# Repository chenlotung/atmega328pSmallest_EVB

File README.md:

# 自已的開發板自己做工作坊
## 裸線焊接你的Atmega328p迷你開發板
[工作訪計畫書_hackmd](https://hackmd.io/4ialXZNIRGWbu7fYnHaSIw?both)

[單層板設計_kicad_github](https://github.com/chenlotung/atmega328pSmallest_EVB)
- kicad 3d模型圖
- 

# 所需材料(粗估成本:每份230元不含運，不含uno板及焊接工具)
- [ ] arduino uno r3 開發板
- [ ] cp2102 usb to ttl 模組
- [ ] atmega328p dip 28pin
- [ ] 5x7cm以上，單面或雙面玻纖萬孔板
- [ ] 16MHZ 石英震盪器
- [ ] 18-22pF陶瓷電容*2
- [ ] 長杜邦針or母座*28
- [ ] 5mmLED
- [ ] 5X6mm直插式按鈕*2
- [ ] 電阻(下列各一)
- 1k,1M.10M 
- [ ] 鍍錫裸線
- [ ] 焊錫

# 實驗步驟
1. 元件測試
    -  led、按鈕通斷測試
    -  電容值電阻值紀錄
    -  使用麵包板與uno燒錄bootloader 確認晶片功能正常

定位各元件位置，（參照參考資料之位置圖與走線圖)

未完待續...................
未完成項目:底座製圖(四角拔模圓柱，矩形底座)
# 參考資料
## 照片 
- atmega328p pin out

- arduino uno r3 schematic

- 萬孔板正面元件位置圖
- 

- 萬孔板背面走線圖
- 

## 影片

* [燒錄BootLoader](https://www.youtube.com/watch?v=smr9EddIL3Q)
* [上傳程式](https://www.youtube.com/watch?v=cvyq-qohljg)
## 文章
https://www.instructables.com/%E8%87%AA%E9%80%A0%E4%BD%A0%E7%9A%84Arduino-UNO%E6%9D%BF/
https://www.microchip.com/en-us/product/ATmega328P#document-table
https://www.electroschematics.com/diy-arduino-making-your-own-arduino/
https://makersportal.com/blog/2018/3/15/arduino-internet-of-things-part-1-burning-the-arduino-bootloader-onto-a-blank-atmega328p-chip-using-the-arduino-uno

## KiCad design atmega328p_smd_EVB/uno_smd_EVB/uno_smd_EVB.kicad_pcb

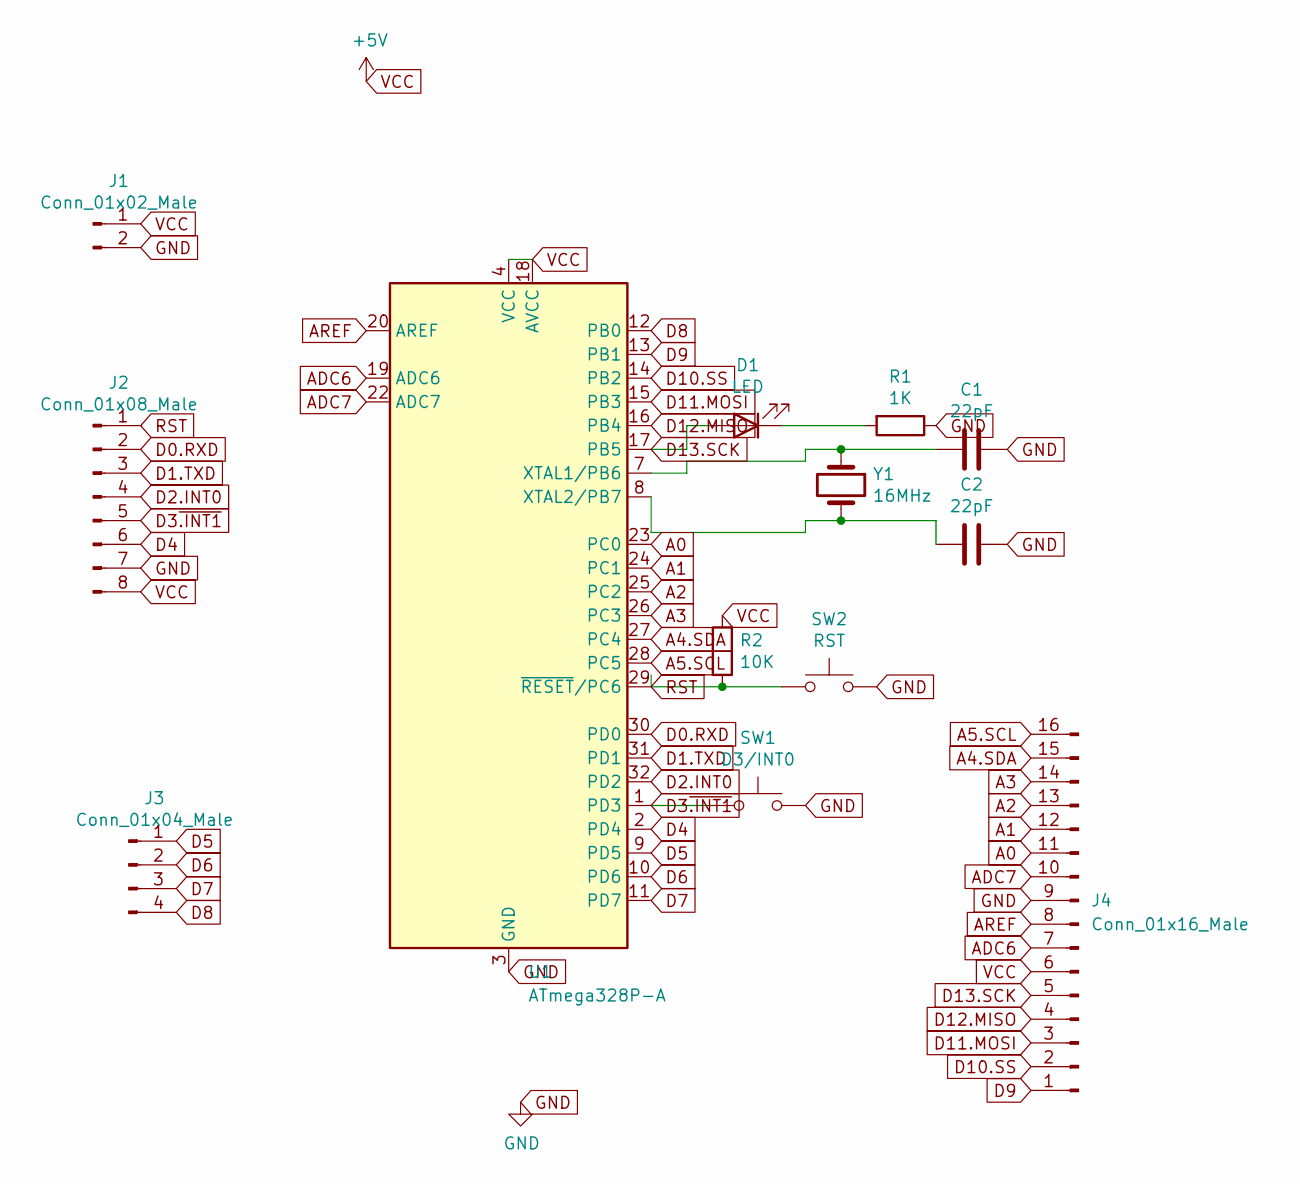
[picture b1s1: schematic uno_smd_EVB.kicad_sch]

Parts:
C1, C2: 22pF; C_0805_2012Metric_Pad1.18x1.45mm_HandSolder
D1: LED; LED_0805_2012Metric_Pad1.15x1.40mm_HandSolder
J1: Conn_01x02_Male; PinHeader_1x02_P2.54mm_Vertical
J2: Conn_01x08_Male; PinHeader_1x08_P2.54mm_Vertical
J3: Conn_01x04_Male; PinHeader_1x04_P2.54mm_Vertical
J4: Conn_01x16_Male; PinHeader_1x16_P2.54mm_Vertical
R1: 1K; R_0805_2012Metric_Pad1.20x1.40mm_HandSolder
R2: 10K; R_0805_2012Metric_Pad1.20x1.40mm_HandSolder
SW1: D3/INT0; SW_SPST_TL3342
SW2: RST; SW_SPST_TL3342
U1: ATmega328P-A; TQFP-32_7x7mm_P0.8mm
Y1: 16MHz; Crystal_SMD_HC49-SD

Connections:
A0: J4.11, U1.23 (PC0)
A1: J4.12, U1.24 (PC1)
A2: J4.13, U1.25 (PC2)
A3: J4.14, U1.26 (PC3)
A4.SDA: J4.15, U1.27 (PC4)
A5.SCL: J4.16, U1.28 (PC5)
ADC6: J4.7, U1.19 (ADC6)
ADC7: J4.10, U1.22 (ADC7)
AREF: J4.8, U1.20 (AREF)
D0.RXD: J2.2, U1.30 (PD0)
D1.TXD: J2.3, U1.31 (PD1)
D2.INT0: J2.4, U1.32 (PD2)
D3~.INT1: J2.5, SW1.1, U1.1 (PD3)
D4: J2.6, U1.2 (PD4)
D5~{: J3.1, U1.9 (PD5)
D6: J3.2, U1.10 (PD6)
D7: J3.3, U1.11 (PD7)
D8: J3.4, U1.12 (PB0)
D9: J4.1, U1.13 (PB1)
D10.SS: J4.2, U1.14 (PB2)
D11.MOSI: J4.3, U1.15 (PB3)
D12.MISO: J4.4, U1.16 (PB4)
D13.SCK: D1.2 (A), J4.5, U1.17 (PB5)
GND: C1.1, C2.1, J1.2, J2.7, J4.9, R1.1, SW1.2, SW2.2, U1.3 (GND), U1.5 (GND), U1.21 (GND)
unnamed: C1.2, U1.7 (XTAL1/PB6), Y1.1
unnamed: C2.2, U1.8 (XTAL2/PB7), Y1.2
unnamed: D1.1 (K), R1.2
RST: J2.1, R2.2, SW2.1, U1.29 (~RESET/PC6)
VCC: J1.1, J2.8, J4.6, R2.1, U1.4 (VCC), U1.6 (VCC), U1.18 (AVCC)

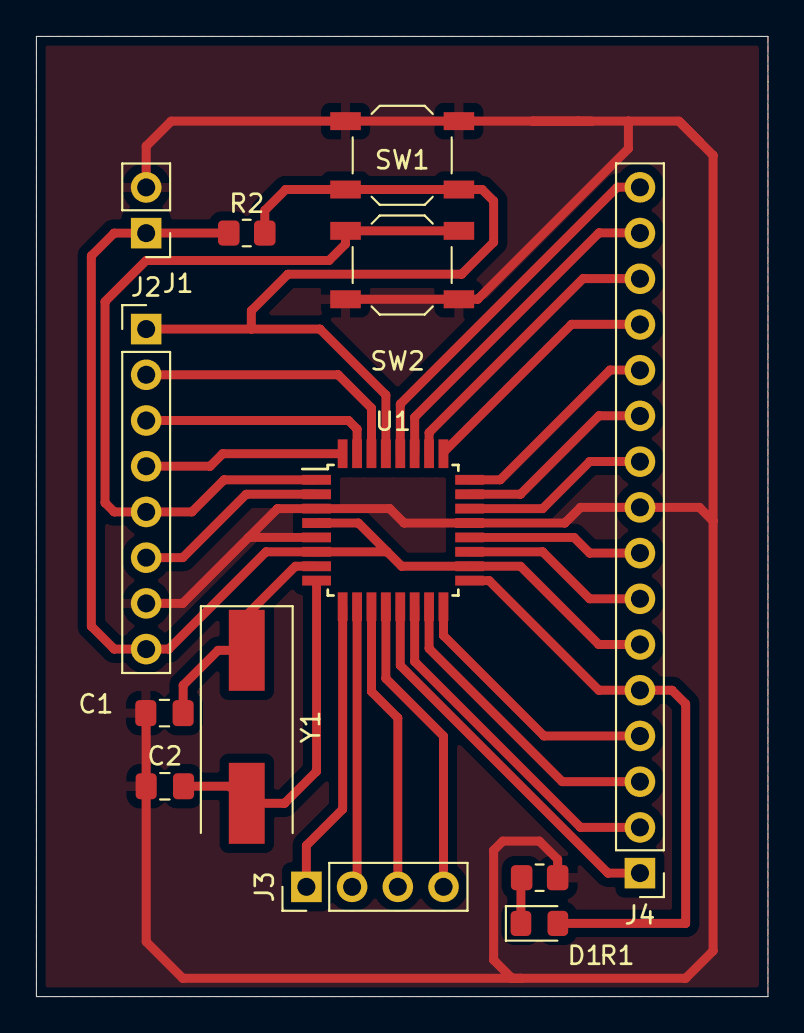
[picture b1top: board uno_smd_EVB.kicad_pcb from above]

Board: 2 copper layers, 40.6 x 53.3 mm, 13 parts (0 on the bottom side), 29 nets.

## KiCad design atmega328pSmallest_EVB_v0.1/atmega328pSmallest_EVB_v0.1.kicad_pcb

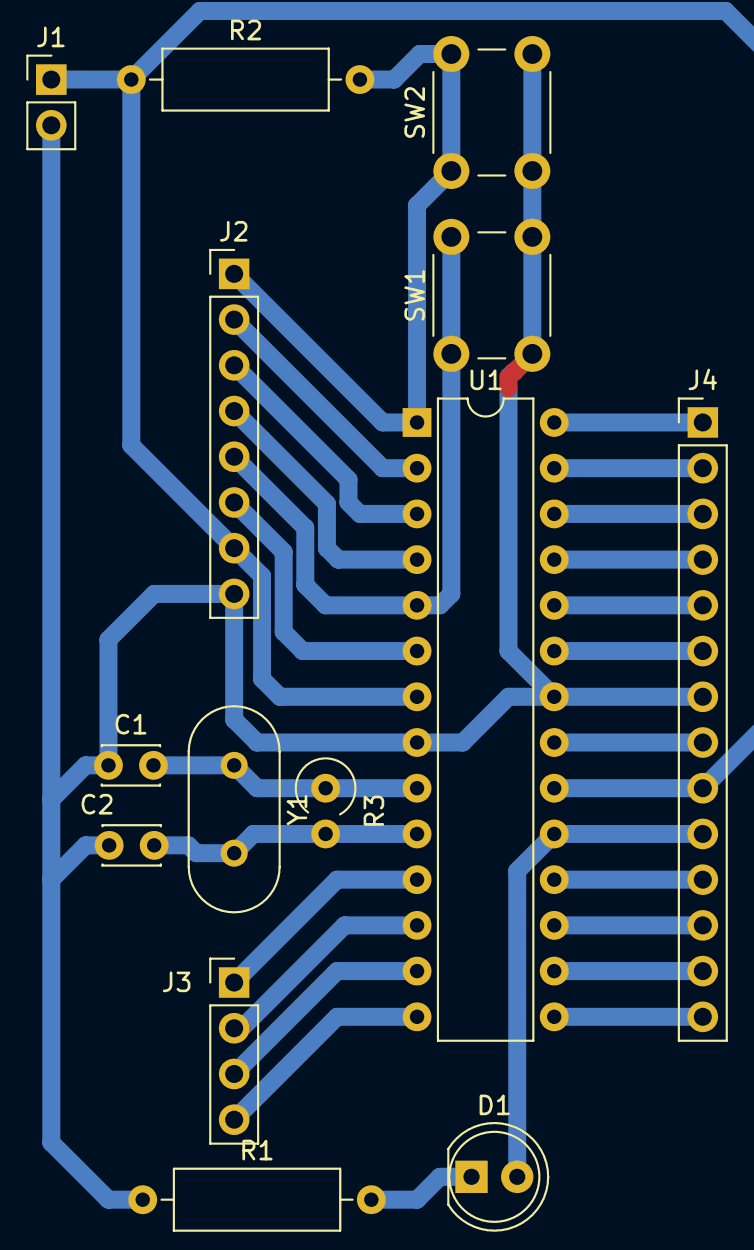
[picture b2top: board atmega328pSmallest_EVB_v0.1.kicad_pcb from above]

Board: 2 copper layers, 14 parts (0 on the bottom side), 27 nets.

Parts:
C1, C2: 22pF; C_Disc_D3.0mm_W2.0mm_P2.50mm
D1: LED; LED_D5.0mm_Clear
J1: Conn_01x02_Male; PinHeader_1x02_P2.54mm_Vertical
J2: Conn_01x08_Male; PinHeader_1x08_P2.54mm_Vertical
J3: Conn_01x04_Male; PinHeader_1x04_P2.54mm_Vertical
J4: Conn_01x14_Male; PinHeader_1x14_P2.54mm_Vertical
R1: 1K; R_Axial_DIN0309_L9.0mm_D3.2mm_P12.70mm_Horizontal
R2: 10K; R_Axial_DIN0309_L9.0mm_D3.2mm_P12.70mm_Horizontal
R3: 1M; R_Axial_DIN0309_L9.0mm_D3.2mm_P2.54mm_Vertical
SW1: D3/INT0; SW_PUSH_6mm_H5mm
SW2: RST; SW_PUSH_6mm_H5mm
U1: ATmega328P-PU; DIP-28_W7.62mm
Y1: 16MHz; Crystal_HC49-4H_Vertical

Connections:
A0: J4.6, U1.23
A1: J4.5, U1.24
A2: J4.4, U1.25
A3: J4.3, U1.26
A4.SDA: J4.2, U1.27
A5.SCL: J4.1, U1.28
AREF: J4.8, U1.21
D0.RXD: J2.2, U1.2
D1.TXD: J2.3, U1.3
D2.INT0: J2.4, U1.4
D3~.INT1: J2.5, SW1.1, U1.5
D4: J2.6, U1.6
D5~: J3.1, U1.11
D6: J3.2, U1.12
D7: J3.3, U1.13
D8: J3.4, U1.14
D9: J4.14, U1.15
D10.SS: J4.13, U1.16
D11.MOSI: J4.12, U1.17
D12.MISO: J4.11, U1.18
D13.SCK: D1.2, J4.10, U1.19
GND: C1.1, C2.1, J1.2, J2.8, J4.7, R1.1, SW1.2, SW2.2, U1.8, U1.22
unnamed: C1.2, R3.1, U1.9, Y1.1
unnamed: C2.2, R3.2, U1.10, Y1.2
unnamed: D1.1, R1.2
RST: J2.1, R2.2, SW2.1, U1.1
VCC: J1.1, J2.7, J4.9, R2.1, U1.7, U1.20

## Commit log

2021-09-20 main kicad project
2021-09-20 PDF for Circuit diagram and single layer PCB
2021-09-20 update from hackmd_20210920
2021-09-20 update hackmd link
2021-09-20 V0.1_first test_20210920
2021-09-20 EVB V0.1's gerber file
2021-09-20 kicad's 3D picture and Soldering photos
2021-09-20 ardinoISP,blink
2021-09-20 wrong add
2021-09-20 Arduino example code ,arduinoISP and blink
2021-09-22 V0.1_20210922
2022-02-17 Create 1
2022-02-17 just test
2022-02-17 V0.2_smd_version
